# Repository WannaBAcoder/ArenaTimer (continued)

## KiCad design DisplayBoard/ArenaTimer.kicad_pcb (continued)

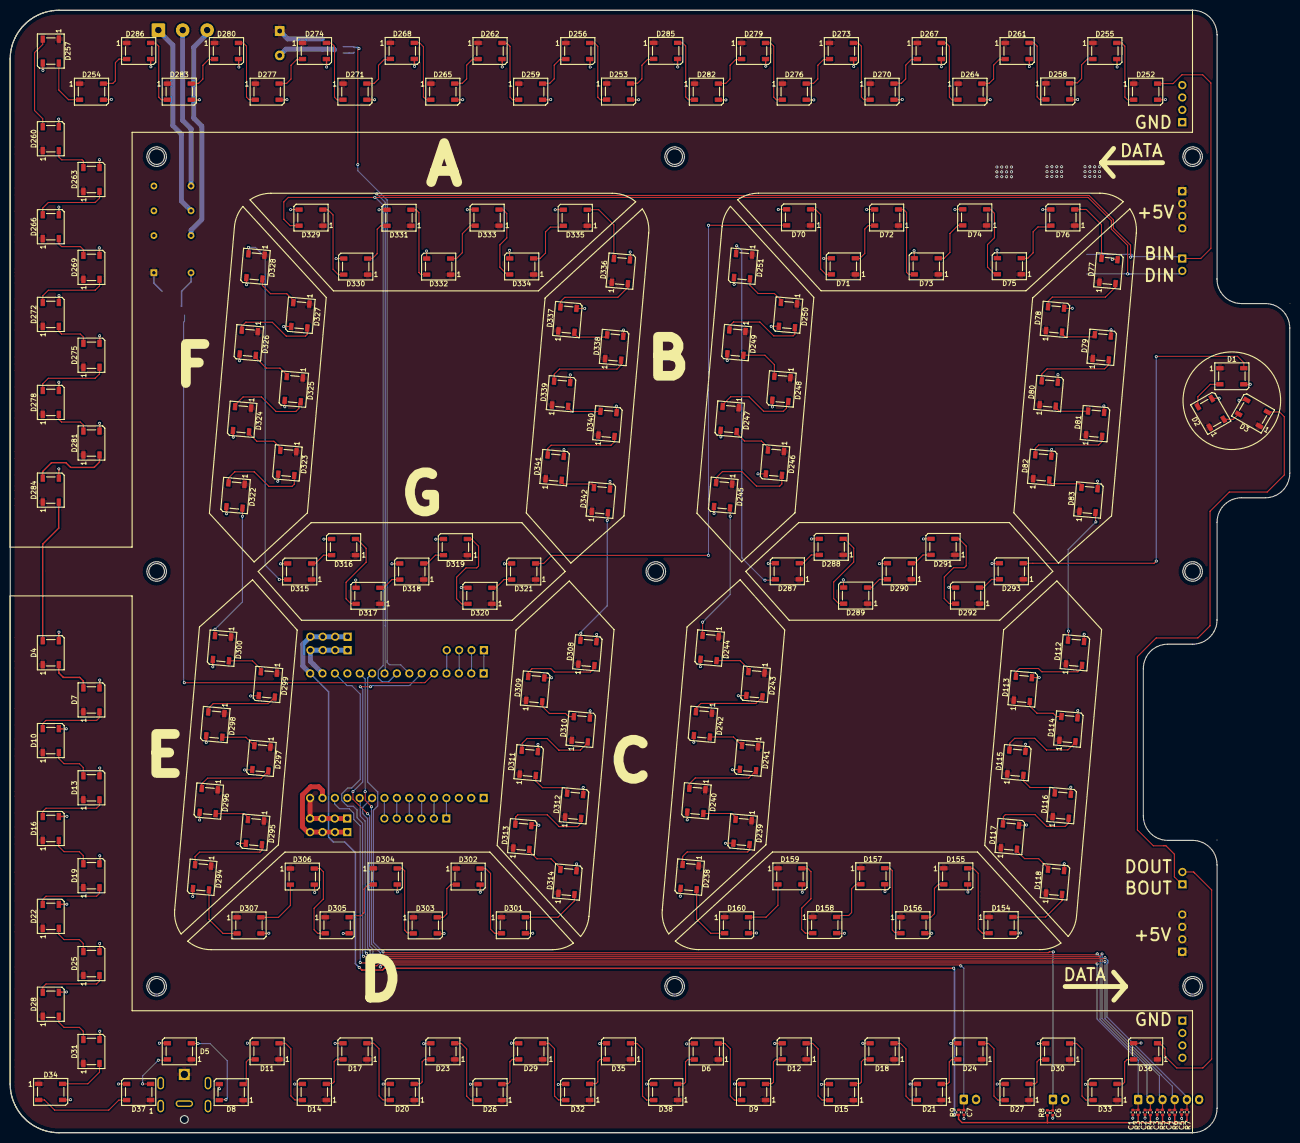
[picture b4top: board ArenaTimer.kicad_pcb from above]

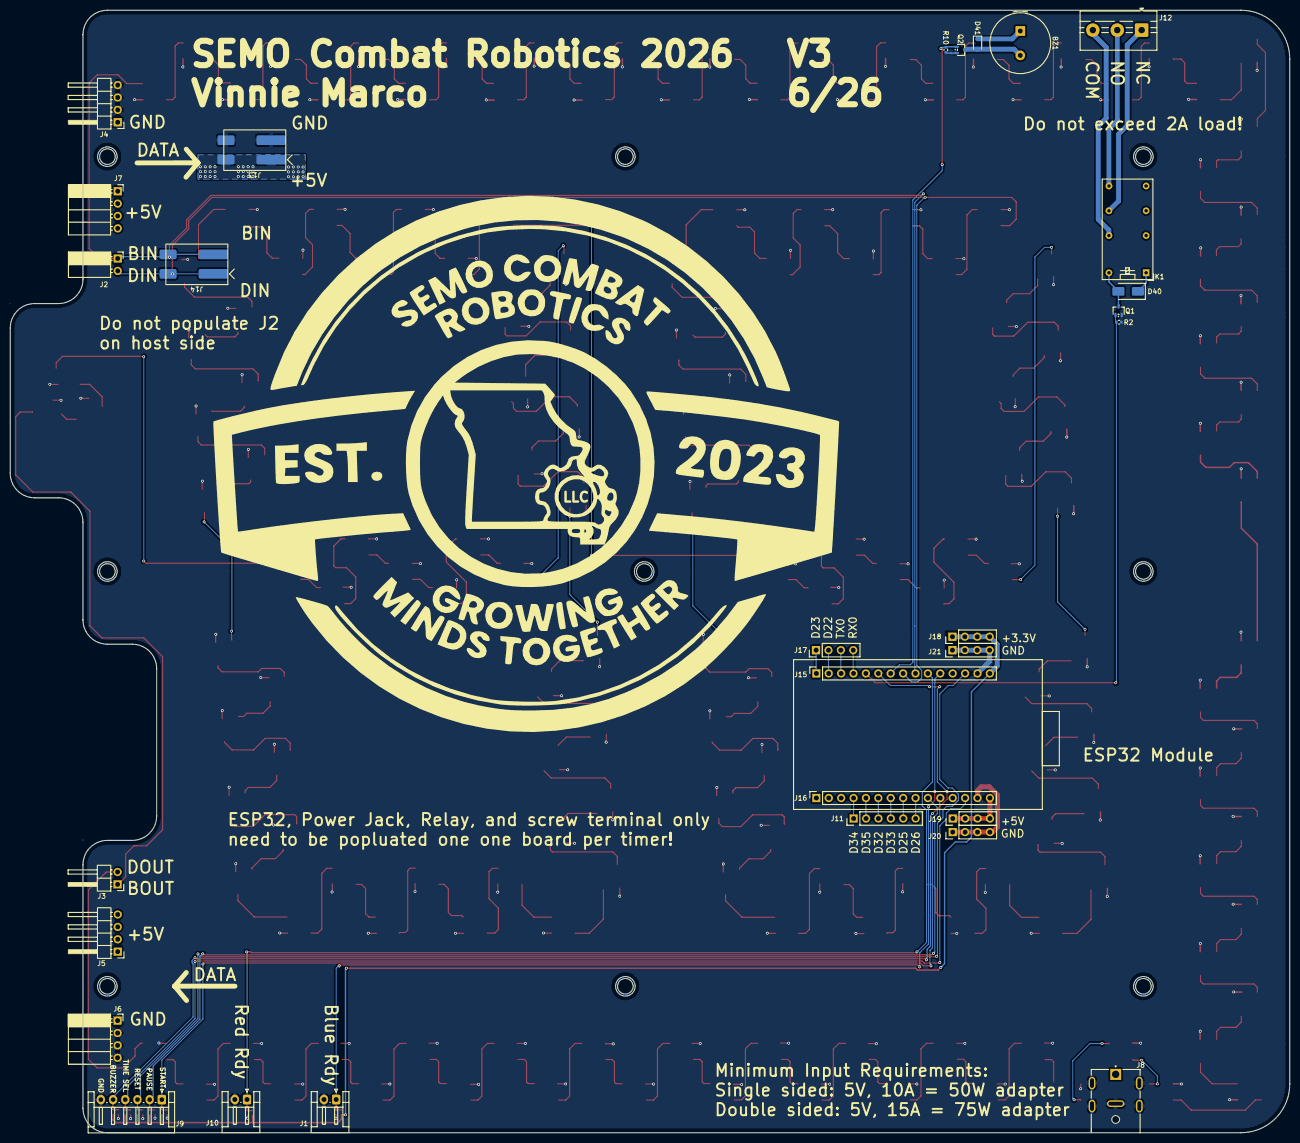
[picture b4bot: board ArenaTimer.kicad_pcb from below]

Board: 2 copper layers, 262.2 x 230.0 mm, 223 parts (29 on the bottom side), 200 nets.

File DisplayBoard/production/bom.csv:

Designator,Footprint,Quantity,Value,LCSC Part #
"C1, C2, C3, C4, C5, C6, C7",0402,7,100nF,C14663
"D1, D10, D11, D112, D113, D114, D115, D116, D117, D118, D12, D13, D14, D15, D154, D155, D156, D157, D158, D159, D16, D160, D17, D18, D19, D2, D20, D21, D22, D23, D238, D239, D24, D240, D241, D242, D243, D244, D245, D246, D247, D248, D249, D25, D250, D251, D252, D253, D254, D255, D256, D257, D258, D259, D26, D260, D261, D262, D263, D264, D265, D266, D267, D268, D269, D27, D270, D271, D272, D273, D274, D275, D276, D277, D278, D279, D28, D280, D281, D282, D283, D284, D285, D286, D287, D288, D289, D29, D290, D291, D292, D293, D294, D295, D296, D297, D298, D299, D3, D30, D300, D301, D302, D303, D304, D305, D306, D307, D308, D309, D31, D310, D311, D312, D313, D314, D315, D316, D317, D318, D319, D32, D320, D321, D322, D323, D324, D325, D326, D327, D328, D329, D33, D330, D331, D332, D333, D334, D335, D336, D337, D338, D339, D34, D340, D341, D342, D35, D36, D37, D38, D4, D5, D6, D7, D70, D71, D72, D73, D74, D75, D76, D77, D78, D79, D8, D80, D81, D82, D83, D9",LED_WS2812B_PLCC4_5.0x5.0mm_P3.2mm,171,WS2812B,C2843785
D40,D_SMA,1,"1N1007, SMA",C727081
D41,D_SOD-323,1,"1N4148WS, SOD323",C2128
J1,JST_EH_S2B-EH_1x02_P2.50mm_Horizontal,1,Blue ready-up,C19271377
J10,JST_EH_S2B-EH_1x02_P2.50mm_Horizontal,1,Red ready-up,C19271377
"J13, J14",2060-452_998-404,2,WAGO,C2765055
"J15, J16",PinSocket_1x15_P2.54mm_Vertical,2,Conn_01x15_Socket,C124408
J2,PinSocket_1x02_P2.54mm_Horizontal,1,Conn_01x02_Socket,C2897384
J3,PinHeader_1x02_P2.54mm_Horizontal,1,Conn_01x02_Pin,C492410
J4,PinHeader_1x04_P2.54mm_Horizontal,1,GND,C492412
J5,PinHeader_1x04_P2.54mm_Horizontal,1,5V,C492412
J6,PinSocket_1x04_P2.54mm_Horizontal,1,GND,C2897386 
J7,PinSocket_1x04_P2.54mm_Horizontal,1,5V,C2897386 
J9,JST_EH_S6B-EH_1x06_P2.50mm_Horizontal,1,Conn_01x06_Pin,C157919
"Q1, Q2",SOT-323_SC-70,2,BSS138,C5224267
"R10, R2",0402,2,100K,C25530
"R3, R4, R5, R6, R7, R8, R9",0402,7,10k,C25744

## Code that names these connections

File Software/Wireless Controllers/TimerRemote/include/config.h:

#ifndef CONFIG_H
#define CONFIG_H

#include <Arduino.h>

// Button GPIOs (STM32G030K8T6, see PCB Files/TimerRemote netlist).
// All buttons are 1:1 GPIO-to-GND, active low, need INPUT_PULLUP.
#define PIN_START PB1
#define PIN_PAUSE PA5
// PA6 is the board's power button. The Judge's RESET (SW3) and the ready
// remote's only button (SW6) both land on this net, and either one also
// pulls the BQ24075's SYSOFF low through D1 to power the board on. It is
// therefore a dual-use button: tap = command, long hold = power off.
#define PIN_RESET PA6
#define PIN_TSEL PA7
#define PIN_BUZZ PB0

// Power latch (Q3 gate, 100k pull-down R15). HIGH holds SYSOFF low = board
// stays on after the power button is released. LOW releases it; the board
// then loses power as soon as the button is up (and USB is absent).
#define PIN_PWR_EN PA15

// Blue status LED (D11). Its anode is on VSYS and its cathode goes through
// R18 (470R) to this pin, so it is ACTIVE LOW: drive LOW = on, release the
// pin (INPUT) = off.
#define PIN_STATUS_LED PA8

// Battery sense: VSYS through R21/R22 (1M/1M, so the pin sees VSYS / 2) with
// C9 (100nF) on the node. VSYS tracks VBAT within ~tens of mV while running
// from battery.
#define PIN_BATT_SENSE PA4
#define BATT_DIVIDER_RATIO 2

// Role/variant solder jumpers RA1 / RB1: 0R to GND when fitted, otherwise
// the pin reads HIGH with the internal pull-up. Sampled once at boot, then
// returned to analog mode so they cost nothing while asleep. See
// roleConfig.h for which state means what.
#define PIN_ROLE_JUDGE PB7 // RA1
#define PIN_ROLE_COLOR PB8 // RB1

// RA-08H control
#define PIN_RADIO_RST PA1
// RA-08H BOOT/IO2 (R20 10k pulls it low). Driven HIGH by the STM32 only
// while it resets the radio into its ROM bootloader to (re)flash it.
#define PIN_RADIO_BOOT PA3
// Hard limit: the module's AT interface runs on its LPUART, which cannot
// exceed 9600 baud. Must match the RA08H_p2p_bridge firmware.
#define RADIO_BAUD 9600
// UART to RA-08H is USART1: PA9 TX (-> module LPRXD), PA10 RX (<- module TXD).
//
// IMPORTANT: this package has two physical pads that can each carry PA9 (and
// likewise for PA10) - the plain, default-location pad, and a second,
// "remapped" pad selectable via the chip's pin-remap feature. Per the actual
// PCB netlist (PCB Files/TimerRemote), the radio is wired to the REMAPPED
// pads, not the default ones - the default PA9/PA10 pads go nowhere (net
// "unconnected-(U2-NC/PA9-Pad19)" etc). Arduino's plain PA9/PA10 macros
// resolve to the default (unconnected) pads, so using them here compiles and
// runs but talks to a floating pin - the radio never receives anything and
// the STM32 never sees a reply, with no error either side. PA_9_R/PA_10_R
// (defined in the STM32duino variant's PinNamesVar.h) are the remap-selected
// PinName values that actually land on the wired pads; HardwareSerial's
// PinName-typed constructor overload is required to use them (the plain
// uint32_t Arduino-pin-number overload can't address a remapped pin).
#define PIN_RADIO_TX PA_9_R
#define PIN_RADIO_RX PA_10_R

// Debug-only, one-way TX broken out to J2 pin 5 (no RX wired)
#define PIN_DEBUG_TX PA2

#endif

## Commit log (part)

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2026-04-27 proof of concept
2026-04-30 implement wireless remotes and controllers with roles
2026-04-30 integrate ESPNOW control into full timer code
2026-05-04 add time edit browser fields
2026-05-10 updated state machine logic
2026-05-11 update controllers to sweep all 11 channels to for sure hit the ESP when connected to wifi
2026-05-11 implement webpage lockouts for different modes to prevent issues during match
2026-05-11 push updated remote code that was missing from last commit
2026-05-11 add LED brightness and digit color control
2026-05-11 improve controller sucess rate by transmitting more packets, clean up timer state transition conditions
2026-05-11 added flipped mode support for alternate mounting configs
2026-05-25 update board for next order
2026-05-25 rename some folders
2026-05-25 clean up git history
2026-05-25 clean up duplicated folders
2026-05-25 Permanently delete duplicate folder structure
2026-05-25 update silk
2026-05-25 flip BOUT/DOUT which is techncially flipped, but consistent with legacy HW.
2026-05-26 clean up silk, resolve DRCs
2026-05-27 more cleanup, added spare IO and power pads for expansion
2026-05-28 add beeper, generate production files
2026-05-28 update controller board to include esp8266
2026-05-30 finish controller board and prod files
2026-05-30 finish ready button board and prod files
2026-06-02 fix diode MPN
2026-06-04 update LCSC PN for fets to match sc-70 footprint on board
2026-06-10 export new 3d models of boards
2026-06-21 update 3d model exports
2026-06-23 start to add audio features
2026-06-23 fix clock mode
2026-06-23 fixed pause
2026-06-23 fix unpause
2026-06-25 update controller handling
2026-06-26 add web control for remote buzzer control
2026-06-26 add slave mode
2026-06-26 fix clock mode behavior and graphics
2026-06-27 fix web lockout of slave mode
2026-06-27 remove slave mode stuff for now
2026-06-27 add green border to finished state
2026-06-28 fix reset bug, fix bound remote check bug
2026-06-28 add tapout state audio effect
2026-06-28 set up serial implementation of timer side B
2026-06-29 fixed browser clock lockout bug, finished serial implementation
2026-06-29 fixed countdown display glitch
2026-06-30 broke countdown animation
